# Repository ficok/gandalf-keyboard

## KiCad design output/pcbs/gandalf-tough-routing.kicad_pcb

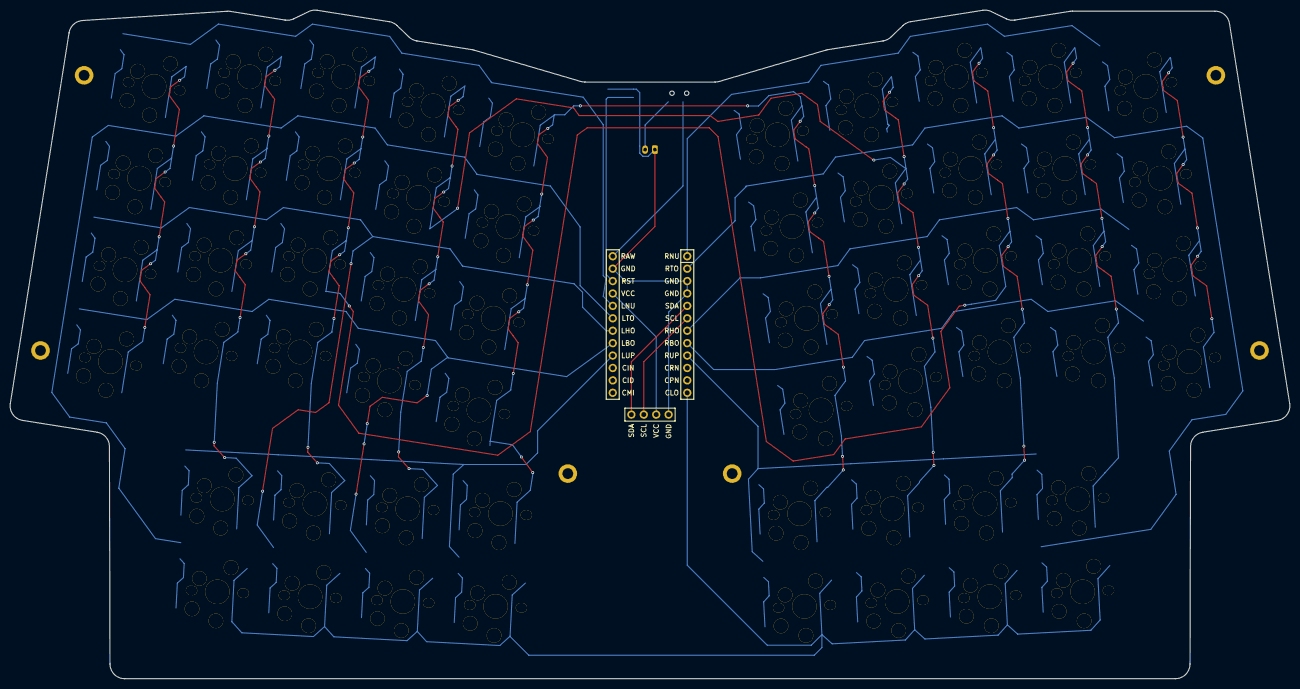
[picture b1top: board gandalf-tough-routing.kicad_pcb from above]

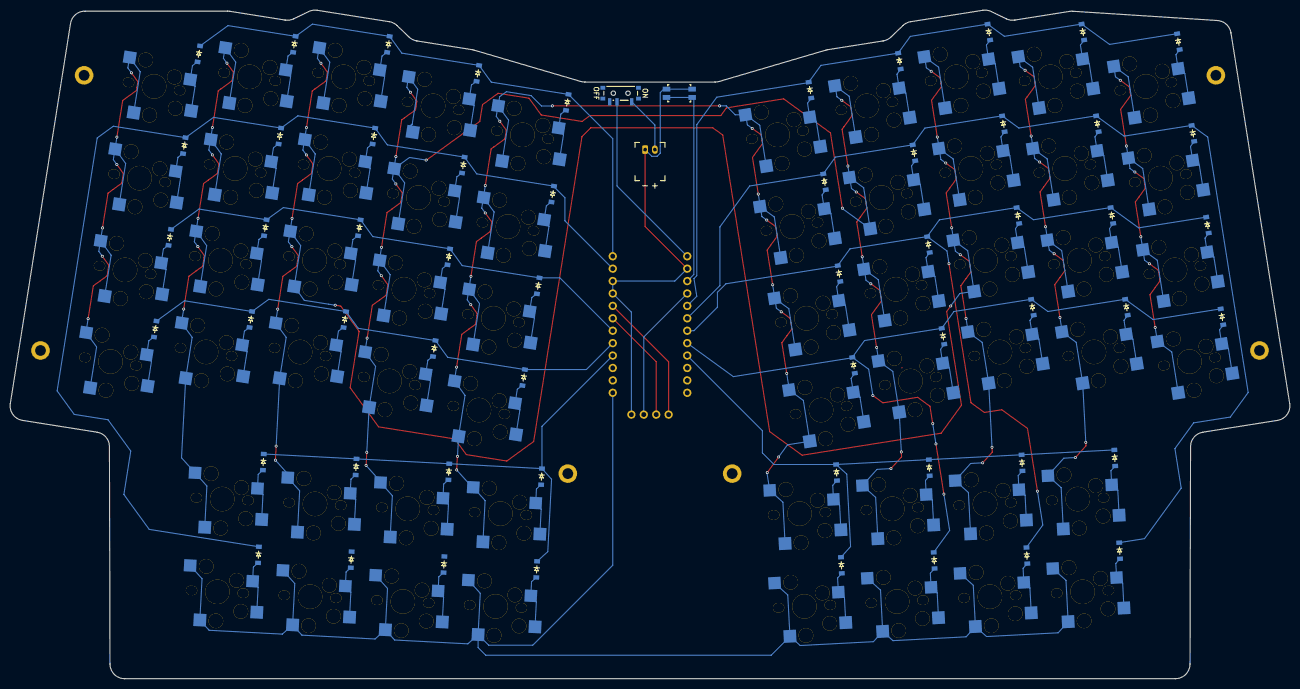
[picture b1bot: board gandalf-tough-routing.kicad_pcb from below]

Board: 2 copper layers, 261.8 x 136.8 mm, 123 parts (115 on the bottom side), 79 nets.

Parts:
D1, D2, D3, D4, D5, D6, D7, D8, D9, D10, D11, D12, D13, D14, D15, D16, D17, D18, D19, D20, D21, D22, D23, D24, D25, D26, D27, D28, D29, D30, D31, D32, D33, D34, D35, D36, D37, D38, D39, D40, D41, D42, D43, D44, D45, D46, D47, D48, D49, D50, D51, D52, D53, D54, D55, D56: diode_tht_sod123
DISP1: display_ssd1306
H1, H2, H3, H4, H5, H6: mounting_hole_plated
JST1: battery_connector_jst_ph_2
MCU1: mcu_nice_nano
PWR1: power_switch_smd_side
RST1: reset_switch_smd_side
S1, S2, S3, S4, S5, S6, S7, S8, S9, S10, S11, S12, S13, S14, S15, S16, S17, S18, S19, S20, S21, S22, S23, S24, S25, S26, S27, S28, S29, S30, S31, S32, S33, S34, S35, S36, S37, S38, S39, S40, S41, S42, S43, S44, S45, S46, S47, S48, S49, S50, S51, S52, S53, S54, S55, S56: switch_choc_v1v2_mx

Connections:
BAT_P: JST1.2, PWR1.1
CID: MCU1.14, S13.IN, S14.IN, S15.IN, S16.IN, S33.IN, S34.IN, S35.IN, S36.IN, S46.IN, S54.IN
CIN: MCU1.15, S17.IN, S18.IN, S19.IN, S20.IN, S37.IN, S38.IN, S39.IN, S40.IN, S48.IN, S56.IN
CLO: MCU1.12, S41.IN, S43.IN, S45.IN, S47.IN, S49.IN, S51.IN, S53.IN, S55.IN
CMI: MCU1.13, S9.IN, S10.IN, S11.IN, S12.IN, S29.IN, S30.IN, S31.IN, S32.IN, S44.IN, S52.IN
CPN: MCU1.11, S1.IN, S2.IN, S3.IN, S4.IN, S21.IN, S22.IN, S23.IN, S24.IN
CRN: MCU1.10, S5.IN, S6.IN, S7.IN, S8.IN, S25.IN, S26.IN, S27.IN, S28.IN, S42.IN, S50.IN
GND: DISP1.4, JST1.1, MCU1.3, MCU1.4, MCU1.23, RST1.1, RST1.3
LBO: D1.IN, D5.IN, D9.IN, D13.IN, D17.IN, D45.IN, MCU1.17
LHO: D2.IN, D6.IN, D10.IN, D14.IN, D18.IN, D43.IN, MCU1.18
LNU: D4.IN, D8.IN, D12.IN, D16.IN, D20.IN, MCU1.20
LTO: D3.IN, D7.IN, D11.IN, D15.IN, D19.IN, D41.IN, MCU1.19
LUP: D42.IN, D44.IN, D46.IN, D47.IN, D48.IN, MCU1.16
RAW: MCU1.24, PWR1.2
RBO: D21.IN, D25.IN, D29.IN, D33.IN, D37.IN, D53.IN, MCU1.8
RHO: D22.IN, D26.IN, D30.IN, D34.IN, D38.IN, D51.IN, MCU1.7
RNU: D24.IN, D28.IN, D32.IN, D36.IN, D40.IN, MCU1.1
RST: MCU1.22, RST1.2, RST1.4
RTO: D23.IN, D27.IN, D31.IN, D35.IN, D39.IN, D49.IN, MCU1.2
RUP: D50.IN, D52.IN, D54.IN, D55.IN, D56.IN, MCU1.9
SCL: DISP1.2, MCU1.6
SDA: DISP1.1, MCU1.5
VCC: DISP1.3, MCU1.21
first_lower: D41.OUT, S41.OUT
first_upper: D42.OUT, S42.OUT
fourth_lower: D47.OUT, S47.OUT
fourth_upper: D48.OUT, S48.OUT
index_bottom: D13.OUT, S13.OUT
index_home: D14.OUT, S14.OUT
index_number: D16.OUT, S16.OUT
index_top: D15.OUT, S15.OUT
inner_bottom: D17.OUT, S17.OUT
inner_home: D18.OUT, S18.OUT
inner_number: D20.OUT, S20.OUT
inner_top: D19.OUT, S19.OUT
middle_bottom: D9.OUT, S9.OUT
middle_home: D10.OUT, S10.OUT
middle_number: D12.OUT, S12.OUT
middle_top: D11.OUT, S11.OUT
mirror_first_lower: D49.OUT, S49.OUT
mirror_first_upper: D50.OUT, S50.OUT
mirror_fourth_lower: D55.OUT, S55.OUT
mirror_fourth_upper: D56.OUT, S56.OUT
mirror_index_bottom: D33.OUT, S33.OUT
mirror_index_home: D34.OUT, S34.OUT
mirror_index_number: D36.OUT, S36.OUT
mirror_index_top: D35.OUT, S35.OUT
mirror_inner_bottom: D37.OUT, S37.OUT
mirror_inner_home: D38.OUT, S38.OUT
mirror_inner_number: D40.OUT, S40.OUT
mirror_inner_top: D39.OUT, S39.OUT
mirror_middle_bottom: D29.OUT, S29.OUT
mirror_middle_home: D30.OUT, S30.OUT
mirror_middle_number: D32.OUT, S32.OUT
mirror_middle_top: D31.OUT, S31.OUT
mirror_pinky_bottom: D21.OUT, S21.OUT
mirror_pinky_home: D22.OUT, S22.OUT
mirror_pinky_number: D24.OUT, S24.OUT
mirror_pinky_top: D23.OUT, S23.OUT
mirror_ring_bottom: D25.OUT, S25.OUT
mirror_ring_home: D26.OUT, S26.OUT
mirror_ring_number: D28.OUT, S28.OUT
mirror_ring_top: D27.OUT, S27.OUT
mirror_second_lower: D51.OUT, S51.OUT
mirror_second_upper: D52.OUT, S52.OUT
mirror_third_lower: D53.OUT, S53.OUT
mirror_third_upper: D54.OUT, S54.OUT
pinky_bottom: D1.OUT, S1.OUT
pinky_home: D2.OUT, S2.OUT
pinky_number: D4.OUT, S4.OUT
pinky_top: D3.OUT, S3.OUT
ring_bottom: D5.OUT, S5.OUT
ring_home: D6.OUT, S6.OUT
ring_number: D8.OUT, S8.OUT
ring_top: D7.OUT, S7.OUT
second_lower: D43.OUT, S43.OUT
second_upper: D44.OUT, S44.OUT
third_lower: D45.OUT, S45.OUT
third_upper: D46.OUT, S46.OUT

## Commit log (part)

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2025-06-02 A wizard is never late
2025-06-02 new fabs and zip
2025-08-06 adding cases
2025-08-07 update cases
2025-08-21 update: add number row and outer column
